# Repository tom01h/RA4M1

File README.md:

# Arduino UNO R4 もどき

## 買ったもの

- [これ(WeActStudio RA4M1)](https://ja.aliexpress.com/item/1005006103872563.html)の3.3V版
- 基板作った
    - LCDとI2C(J8)とUART(J7)とRTC電池(BT1)とSPIフラッシュ(U1)は使えた
    - 他にHX711とつなぐコネクタがある
    - Analog入力も後で試す

## Arduino化

- [Arduino公式のダウンロードページ](https://github.com/arduino/ArduinoCore-renesas/tree/main/bootloaders/UNO_R4)からファームウェア(dfu_minima.hex)をダウンロード
- [Renesas公式のダウンロードページ](https://www.renesas.com/us/en/software-tool/renesas-flash-programmer-programming-gui)からFlash Programmerをダウンロードしてインストール
    - ユーサー登録が必要だった
- [ここ](https://community.element14.com/products/arduino/b/blog/posts/arduino-uno-r4-minima-troubleshooting-unknown-usb-device)のReflash the Bootloader以降に従ってファームウェアを書き込む
    - USBでつなぐ
    - MDボタンを押しながらリセットを押してからはなす（そのあとでMDボタンをはなす）×2回？
        - UARTが生えてくるので番号を覚えておく
    - Flash Programmer起動
        - Connect Settings tabでUARTを選ぶ
        - dfu_minima.hexを読み込む
        - 新しいプロジェクトを作ってセーブ
        - Startを押す (書き込む)
- Example Blinkで確認
    - LED_BUILTINはこのボードにはついていない
    - LED_BUILTINをLED_TXに変更すると動いた（3か所）
- 他にも[サンプルがある](https://github.com/arduino/ArduinoCore-renesas/tree/main/libraries)

## OLED 表示
- SSD1306を使っている[128x32 OLED LCD](https://ja.aliexpress.com/item/32850288143.html)に表示する
- [ここ](https://101010.fun/iot/arduino-oled-display.html)を参考にした
- u8g2ライブラリをインストールする
- GND-＞GND:VCC-＞VCC:100->SCK:101->SDA につなぐ（J4につなぐ）
- OLED.ino を書き込む

## 温湿気圧・CO2濃度計
BME280とMH-Z19をつないで温度・湿度・気圧と二酸化炭素濃度を表示する  
5V電源がないので外部から持ってくる（GNDに注意！！）
- インストールするライブラリ
    - u8g2
    - SparkFun BME280
    - Mzh19 by Eduard
- ピン配は以下の図を参照
- weather.inoを書き込む

## 時計
RTC電池を使って時計を動かす（純正のR4 Minimaには電池繋げません）  
電池ホルターは[これ](https://ja.aliexpress.com/item/4000528748796.html)
- 電池ホルダーBT1にCR1220を入れる
- RTC_AutomaticExample.inoを書き込む
- [バッテリバックアップを使うとき](https://docs.arduino.cc/tutorials/uno-r4-wifi/vrtc-off/)を参考に改変している
- 内蔵クロックを使うと時計の精度がとっても悪いので[外部のオシレータを使う方法](https://me-yoh.com/arduino-uno-r4-rtc-fix)
    - VBATTを使うと外部のオシレータを発振出来ていません

## SPIフラッシュアクセス

[これ](https://ja.aliexpress.com/item/32326265518.html)
- ライブラリは[Arduino-W25Q64](https://github.com/Tamakichi/Arduino-W25Q64)
- READMEに従って手動でライブラリをインストール
- U1につなぐ
- 繋いでいるのはW25Q32だけど使えるらしい
- Arduino-W25Q64.inoを書き込む

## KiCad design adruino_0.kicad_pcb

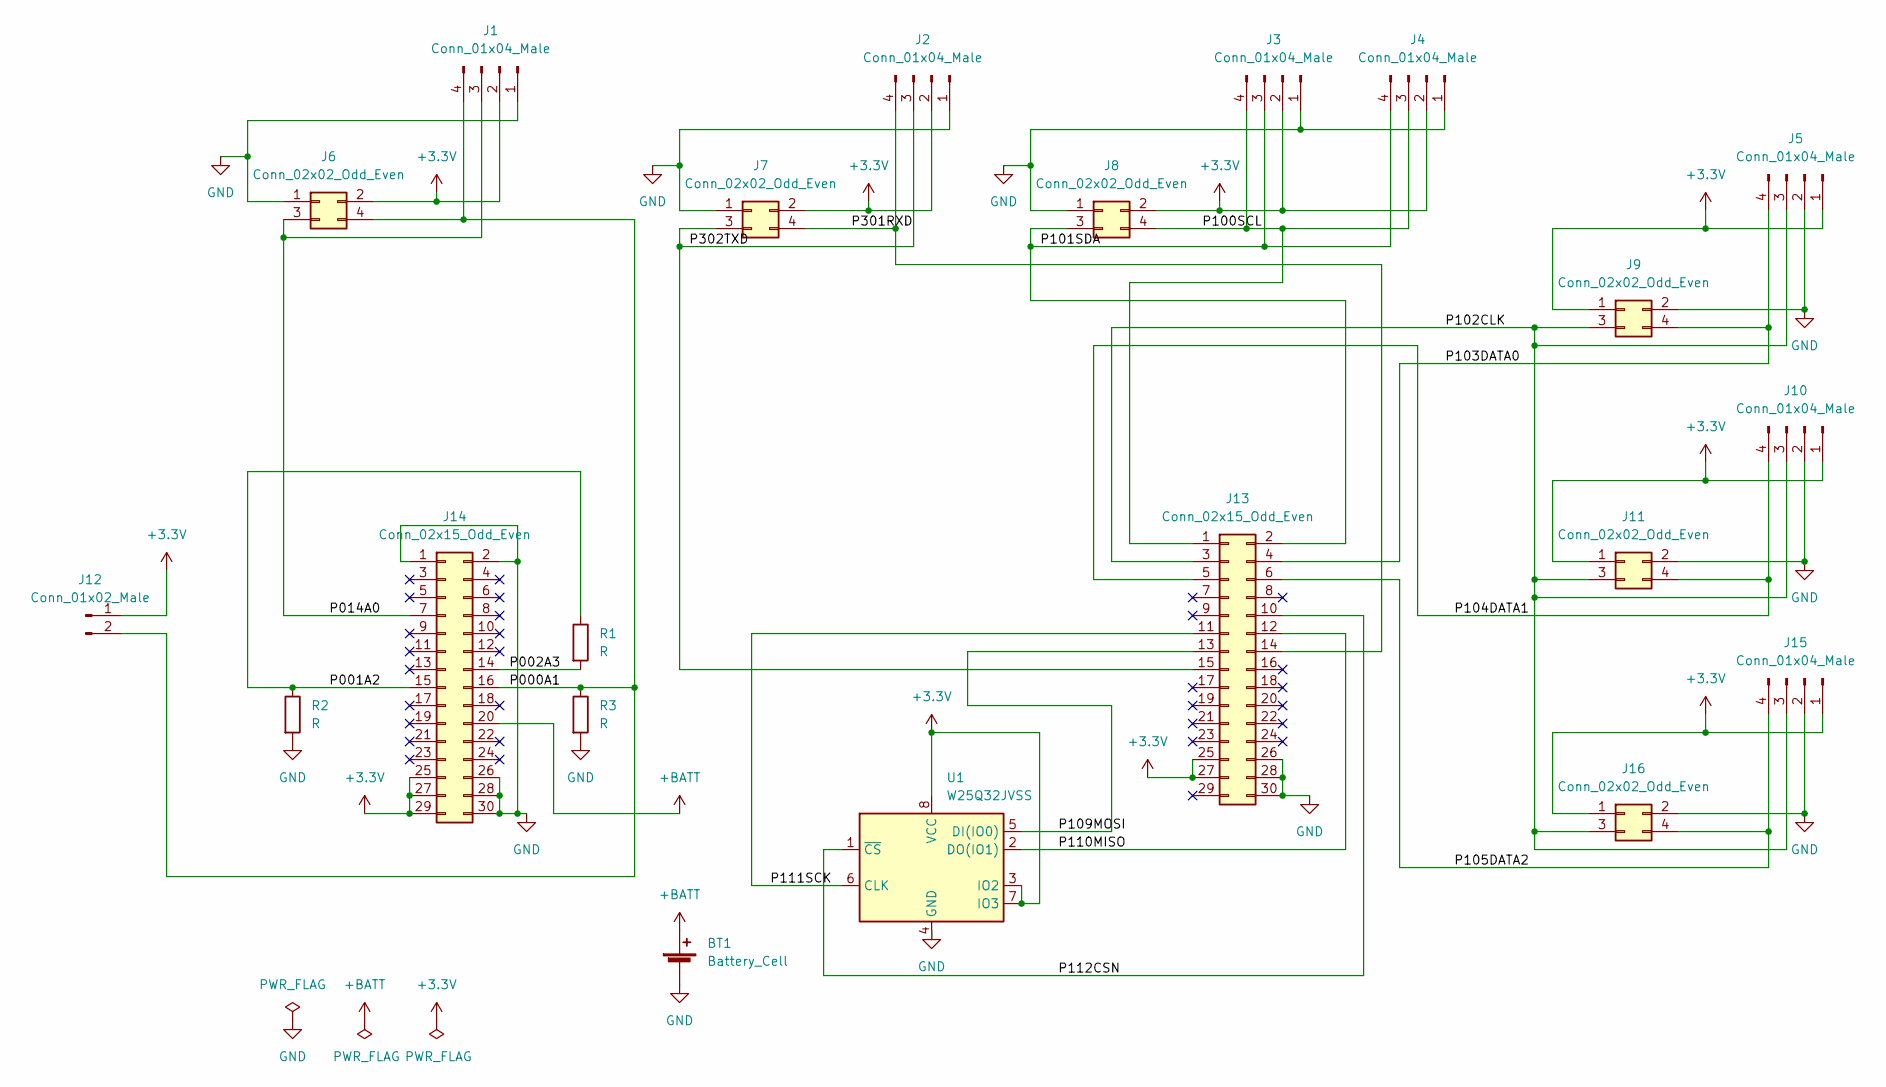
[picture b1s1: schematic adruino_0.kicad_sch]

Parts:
BT1: Battery_Cell; CH291-1220LF
J1, J2, J3, J5, J10, J15: Conn_01x04_Male; JST_PH_S4B-PH-K_1x04_P2.00mm_Horizontal
J4: Conn_01x04_Male; PinHeader_1x04_P2.54mm_Vertical
J6, J7, J8, J9, J11, J16: Conn_02x02_Odd_Even; PinHeader_2x02_P2.54mm_Vertical
J12: Conn_01x02_Male; PinHeader_1x02_P2.54mm_Vertical
J13, J14: Conn_02x15_Odd_Even; PinHeader_2x15_P2.54mm_Vertical
R1, R2, R3: R; R_1206_3216Metric_Pad1.30x1.75mm_HandSolder
U1: W25Q32JVSS; SOIC-8_5.23x5.23mm_P1.27mm

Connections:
+3.3V: J1.2, J2.2, J3.2, J4.2, J5.1, J6.2, J7.2, J8.2, J9.1, J10.1, J11.1, J12.1, J13.25, J13.27, J14.25, J14.27, J14.29, J15.1, J16.1, U1.3 (IO2), U1.7 (IO3), U1.8 (VCC)
+BATT: BT1.1 (+), J14.20
/P000A1: J1.4, J6.4, J12.2, J14.16, R3.1
/P001A2: J14.15, R1.1, R2.1
/P002A3: J14.14, R1.2
/P014A0: J1.3, J6.3, J14.7
/P100SCL: J3.4, J4.3, J8.4, J13.1
/P101SDA: J3.3, J4.4, J8.3, J13.2
/P102CLK: J5.3, J9.3, J10.3, J11.3, J13.3, J15.3, J16.3
/P103DATA0: J5.4, J9.4, J13.4
/P104DATA1: J10.4, J11.4, J13.5
/P105DATA2: J13.6, J15.4, J16.4
/P109MOSI: J13.13, U1.5 (DI(IO0))
/P110MISO: J13.12, U1.2 (DO(IO1))
/P111SCK: J13.11, U1.6 (CLK)
/P112CSN: J13.10, U1.1 (~CS)
/P301RXD: J2.4, J7.4, J13.14
/P302TXD: J2.3, J7.3, J13.15
GND: BT1.2 (-), J1.1, J2.1, J3.1, J4.1, J5.2, J6.1, J7.1, J8.1, J9.2, J10.2, J11.2, J13.26, J13.28, J13.30, J14.1, J14.2, J14.26, J14.28, J14.30, J15.2, J16.2, R2.2, R3.2, U1.4 (GND)

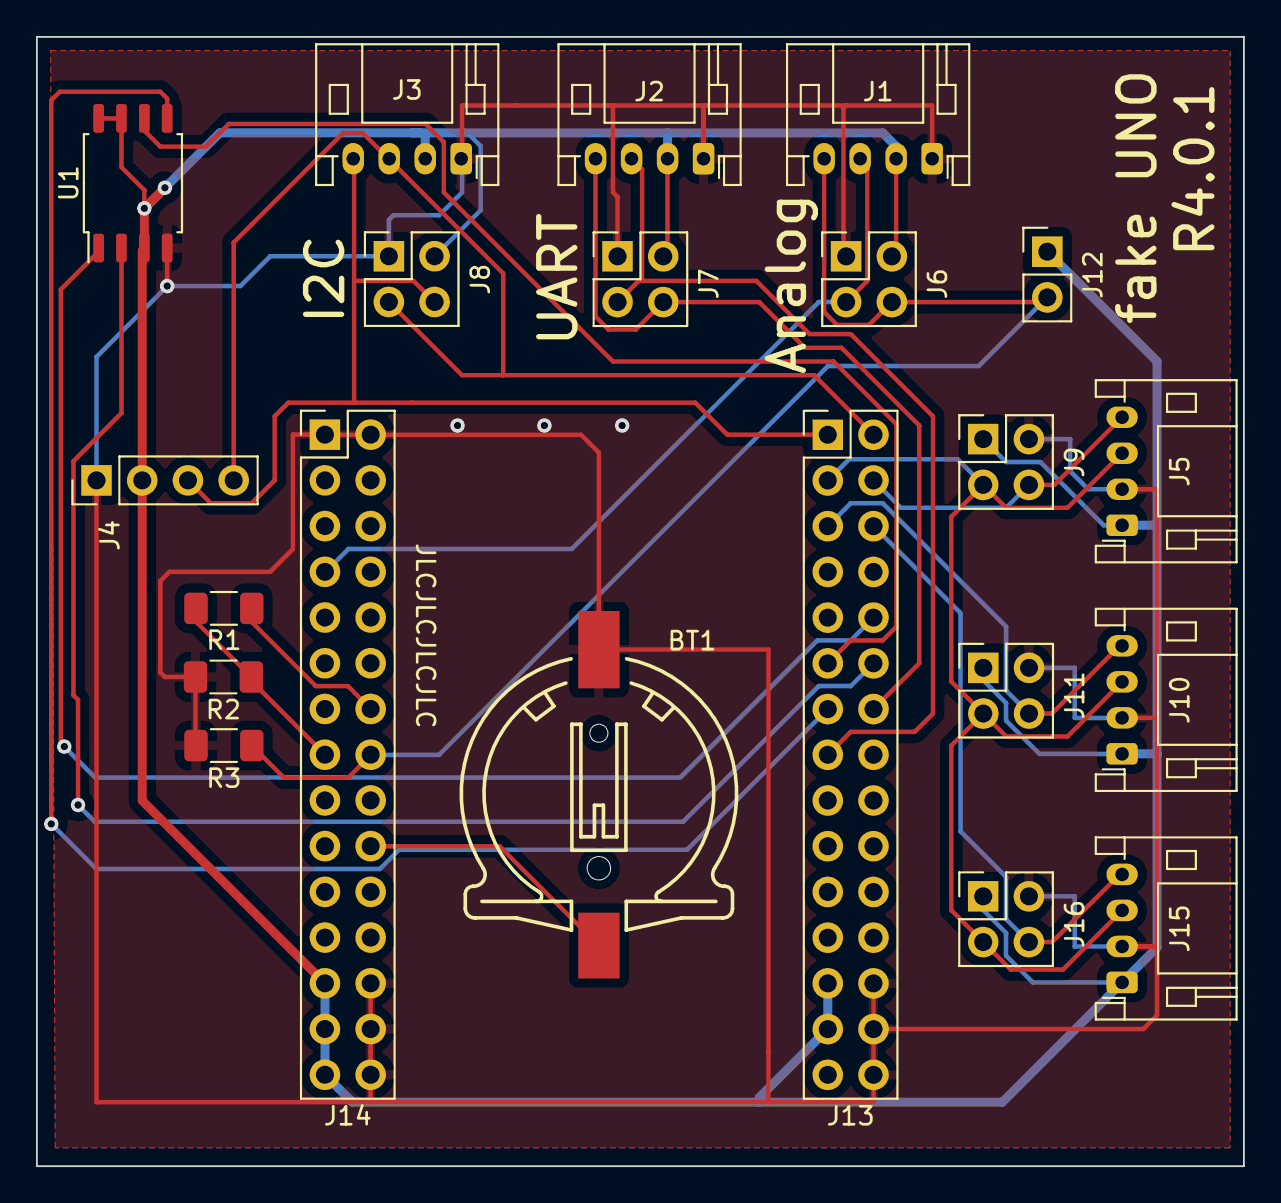
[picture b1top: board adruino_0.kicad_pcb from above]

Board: 2 copper layers, 67.1 x 62.7 mm, 21 parts (0 on the bottom side), 19 nets.

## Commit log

2024-01-22 OLED
2024-01-25 BME280 MZH19
2024-01-25 README
2024-01-29 remove UART
2024-01-31 時計表示修正
2024-01-31 SPIフラッシュ
2024-02-15 基板更新
